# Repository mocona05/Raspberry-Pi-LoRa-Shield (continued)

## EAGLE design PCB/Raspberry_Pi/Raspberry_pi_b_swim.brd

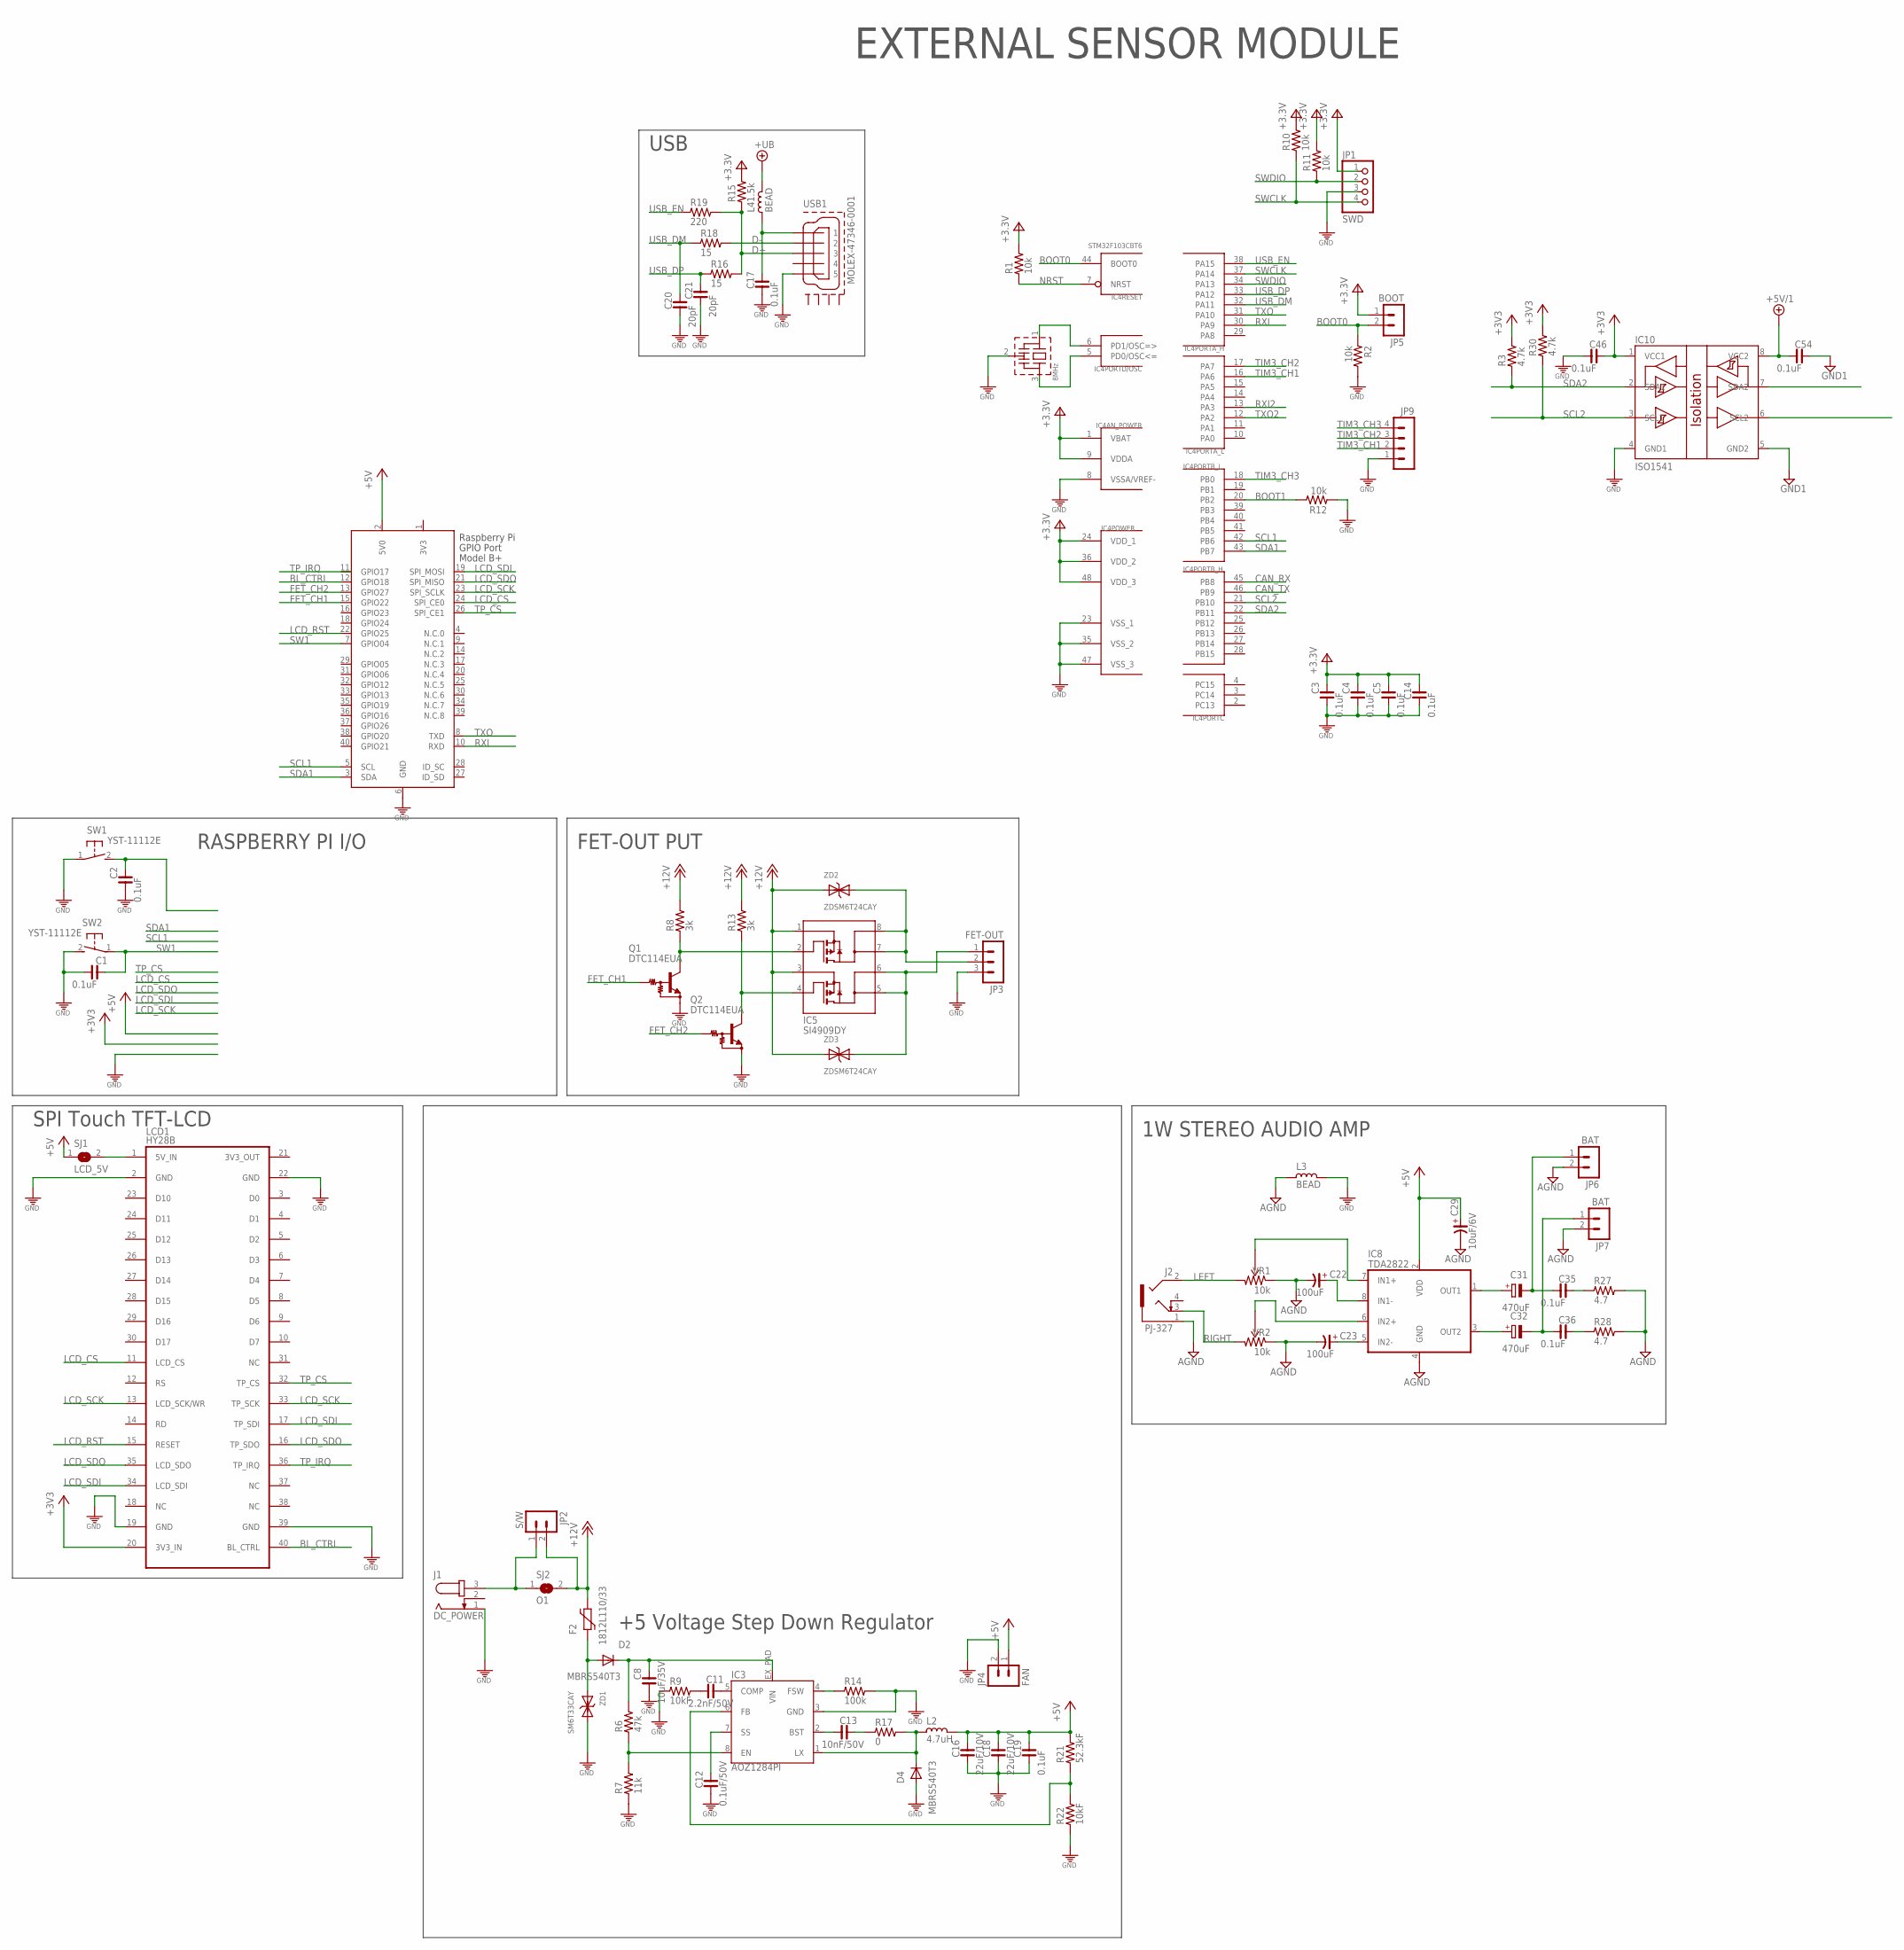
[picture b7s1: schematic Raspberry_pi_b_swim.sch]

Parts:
C1, C2, C3, C4, C5, C14, C17, C19, C35, C36, C46, C54: 0.1uF; C0603
C8: 10uF/35V; C3225
C11: 2.2nF/50V; C0603
C12: 0.1uF/50V; C0603
C13: 10nF/50V; C0603
C16, C18: 22uF/10V; C3216
C20, C21: 20pF; C0603
C22, C23: 100uF; C3528-21/T
C29: 10uF/6V; C3216-18/T
C31, C32: 470uF; D/7343-31W
D2, D4: MBRS540T3; SMC
F2: 1812L110/33; 1812L
IC3: AOZ1284PI; S08-EP1
IC4: STM32F103CBT6; TQFP48
IC5: SI4909DY; SO08-1
IC8: TDA2822; SO08
IC10: ISO1541; SO08
J1: DC_POWER; SPC4077
J2: PJ-327; PJ-327-2
JP1: SWD; 1X04M
JP2: S/W; MA02-MOL-R
JP3: FET-OUT; MA03
JP4: FAN; MA02-MOL-R
JP5: BOOT; MA02-1-MOL
JP6, JP7: BAT; MA02-MOL-R
JP9: MA04-15267; MOLEX5267-04
L2: 4.7uH; L4545
L3: BEAD; L0603
L4: BEAD; L0805
LCD1: HY28B; HY28A
Q1, Q2: DTC114EUA; SC59-BEC
Q3: 8MHz; CSTLA_X
R1, R2, R10, R11, R12: 10k; R0603
R3, R30: 4.7k; R0603
R6: 47k; R0603
R7: 11k; R0603
R8, R13: 3k; R0603
R9, R22: 10kF; R0603
R14: 100k; R0603
R15: 1.5k; R0603
R16, R18: 15; R0603
R17: 0; R0603
R19: 220; R0603
R21: 52.3kF; R0603
R27, R28: 4.7; R0603
SJ1: LCD_5V; SJ
SJ2: O1; SJ
SW1, SW2: YST-11112E; YST-1112E
USB1: MOLEX-47346-0001; MOLEX-47364-0001
VR1, VR2: 10k; R-TRIMMER-3313J
X1: RASPI_BOARD_B+_F; RASPI_BOARD_B+_FULL
ZD1: SM6T33CAY; SMB
ZD2, ZD3: ZDSM6T24CAY; SMB

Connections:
3V3: C3.1, C4.1, C5.1, C14.1, IC4.1 (VBAT), IC4.9 (VDDA), IC4.24 (VDD_1), IC4.36 (VDD_2), IC4.48 (VDD_3), JP1.1, JP5.1, R1.2, R10.2, R11.2, R15.2, X1.1 (3V3)
+3V3: C46.1, IC10.1 (VCC1), LCD1.20 (3V3_IN), R3.2, R30.2
+5V: C16.1, C18.1, C19.1, C29.+, IC8.2 (VDD), JP4.1, L2.1, R21.2, SJ1.1, X1.2 (5V0)
+5V/1: C54.2, IC10.8 (VCC2)
+12V: F2.P$2 (2), IC5.1, IC5.3, JP2.2, R8.2, R13.2, SJ2.2, ZD2.A, ZD3.A
+UB: L4.1
AGND: C22.-, C23.-, C29.-, IC8.4 (GND), J2.1, JP6.2, JP7.2, L3.2, R27.2, R28.2, VR1.1, VR2.1
BL_CTRL: LCD1.40 (BL_CTRL), X1.12 (GPIO18)
BOOT0: IC4.44 (BOOT0), JP5.2, R2.1
BOOT1: IC4.20 (PB2), R12.2
CAN_RX: IC4.45 (PB8)
CAN_TX: IC4.46 (PB9)
D+: R15.1, R16.2, R19.2, USB1.3
D-: R18.2, USB1.2
DC-IN: D2.A, F2.P$1 (1), ZD1.A
FET_CH1: Q1.2 (IN), X1.15 (GPIO22)
FET_CH2: Q2.2 (IN), X1.13 (GPIO27)
GND: C1.2, C2.2, C3.2, C4.2, C5.2, C8.2, C12.2, C14.2, C16.2, C17.2, C18.2, C19.2, C20.2, C21.2, C46.2, D4.A, IC3.3 (GND), IC4.8 (VSSA/VREF-), IC4.23 (VSS_1), IC4.35 (VSS_2), IC4.47 (VSS_3), IC10.4 (GND1), J1.1, JP1.3, JP3.3, JP4.2, JP9.1, L3.1, LCD1.2 (GND), Q1.1 (GND), Q2.1 (GND), Q3.2 (GND), R2.2, R7.1, R9.1, R12.1, R14.2, R22.1, SW1.1, SW2.2, USB1.5, X1.6 (GND), ZD1.C (K)
GND1: C54.1, IC10.5 (GND2)
GND@1: LCD1.19 (GND)
GND@2: LCD1.22 (GND)
GND@3: LCD1.39 (GND)
LCD_CS: LCD1.11 (LCD_CS), X1.24 (SPI_CE0)
LCD_RST: LCD1.15 (RESET), X1.22 (GPIO25)
LCD_SCK: LCD1.13 (LCD_SCK/WR), LCD1.33 (TP_SCK), X1.23 (SPI_SCLK)
LCD_SDI: LCD1.17 (TP_SDI), LCD1.34 (LCD_SDI), X1.19 (SPI_MOSI)
LCD_SDO: LCD1.16 (TP_SDO), LCD1.35 (LCD_SDO), X1.21 (SPI_MISO)
LEFT: J2.2, VR1.3
unnamed: IC4.6 (PD1/OSC=>), Q3.1 (IN)
unnamed: C8.1, D2.C, IC3.EX_PAD (VIN), R6.2
unnamed: IC3.6 (FB), R21.1, R22.2
unnamed: C13.2, IC3.2 (BST)
unnamed: J1.3, JP2.1, SJ2.1
unnamed: IC4.5 (PD0/OSC<=), Q3.3 (OUT)
unnamed: C13.1, R17.1
unnamed: D4.C, IC3.1 (LX), L2.2, R17.2
unnamed: C11.1, IC3.5 (COMP)
unnamed: C11.2, R9.2
unnamed: C2.1, SW1.2
unnamed: IC3.8 (EN), R6.1, R7.2
unnamed: IC5.2, Q1.3 (OUT), R8.1
unnamed: IC3.4 (FSW), R14.1
unnamed: C17.1, L4.2, USB1.1
unnamed: C12.1, IC3.7 (SS)
unnamed: IC5.4, Q2.3 (OUT), R13.1
unnamed: LCD1.1 (5V_IN), SJ1.2
unnamed: C22.+, IC8.8 (IN1-)
unnamed: C23.+, IC8.5 (IN2-)
unnamed: IC8.6 (IN2+), VR2.2
unnamed: IC8.7 (IN1+), VR1.2
unnamed: C31.+, IC8.1 (OUT1)
unnamed: C32.+, IC8.3 (OUT2)
unnamed: C31.-, C35.2, JP6.1
unnamed: C32.-, C36.2, JP7.1
unnamed: C35.1, R27.1
unnamed: C36.1, R28.1
NRST: IC4.7 (NRST), R1.1
RELAY1: IC5.5, IC5.6, JP3.1, ZD3.C (K)
RELAY2: IC5.7, IC5.8, JP3.2, ZD2.C (K)
RIGHT: J2.3, VR2.3
RXI: IC4.30 (PA9), X1.10 (RXD)
RXI2: IC4.13 (PA3)
SCL1: IC4.42 (PB6), X1.5 (SCL)
SCL2: IC4.21 (PB10), IC10.3 (SCL1), R30.1
SCL2-2: IC10.6 (SCL2)
SDA1: IC4.43 (PB7), X1.3 (SDA)
SDA2: IC4.22 (PB11), IC10.2 (SDA1), R3.1
SDA2-2: IC10.7 (SDA2)
SW1: C1.1, SW2.1, X1.7 (GPIO04)
SWCLK: IC4.37 (PA14), JP1.4, R10.1
SWDIO: IC4.34 (PA13), JP1.2, R11.1
TIM3_CH1: IC4.16 (PA6), JP9.2
TIM3_CH2: IC4.17 (PA7), JP9.3
TIM3_CH3: IC4.18 (PB0), JP9.4
TP_CS: LCD1.32 (TP_CS), X1.26 (SPI_CE1)
TP_IRQ: LCD1.36 (TP_IRQ)
TXO: IC4.31 (PA10), X1.8 (TXD)
TXO2: IC4.12 (PA2)
USB_DM: C20.1, IC4.32 (PA11), R18.1
USB_DP: C21.1, IC4.33 (PA12), R16.1
USB_EN: IC4.38 (PA15), R19.1

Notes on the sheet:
SPI Touch TFT-LCD
+5 Voltage Step Down Regulator
RASPBERRY PI I/O
1W STEREO AUDIO AMP
FET-OUT PUT
EXTERNAL SENSOR MODULE
USB

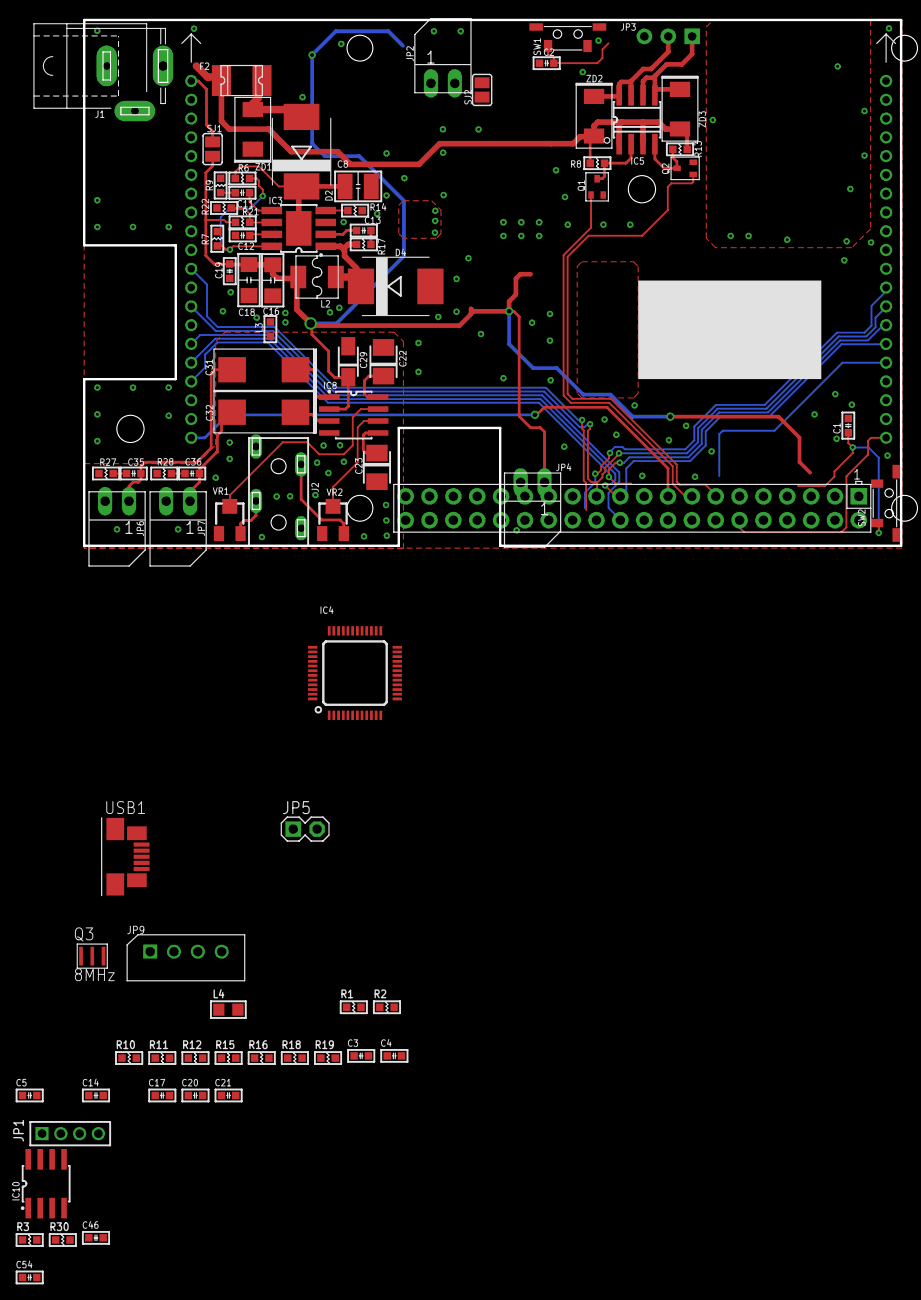
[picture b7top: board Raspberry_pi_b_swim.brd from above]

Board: 2 copper layers, 83 parts (0 on the bottom side), 70 nets.

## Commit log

2018-07-03 저장소 이전후 업로드
2019-03-03 설정파일 업데이트
